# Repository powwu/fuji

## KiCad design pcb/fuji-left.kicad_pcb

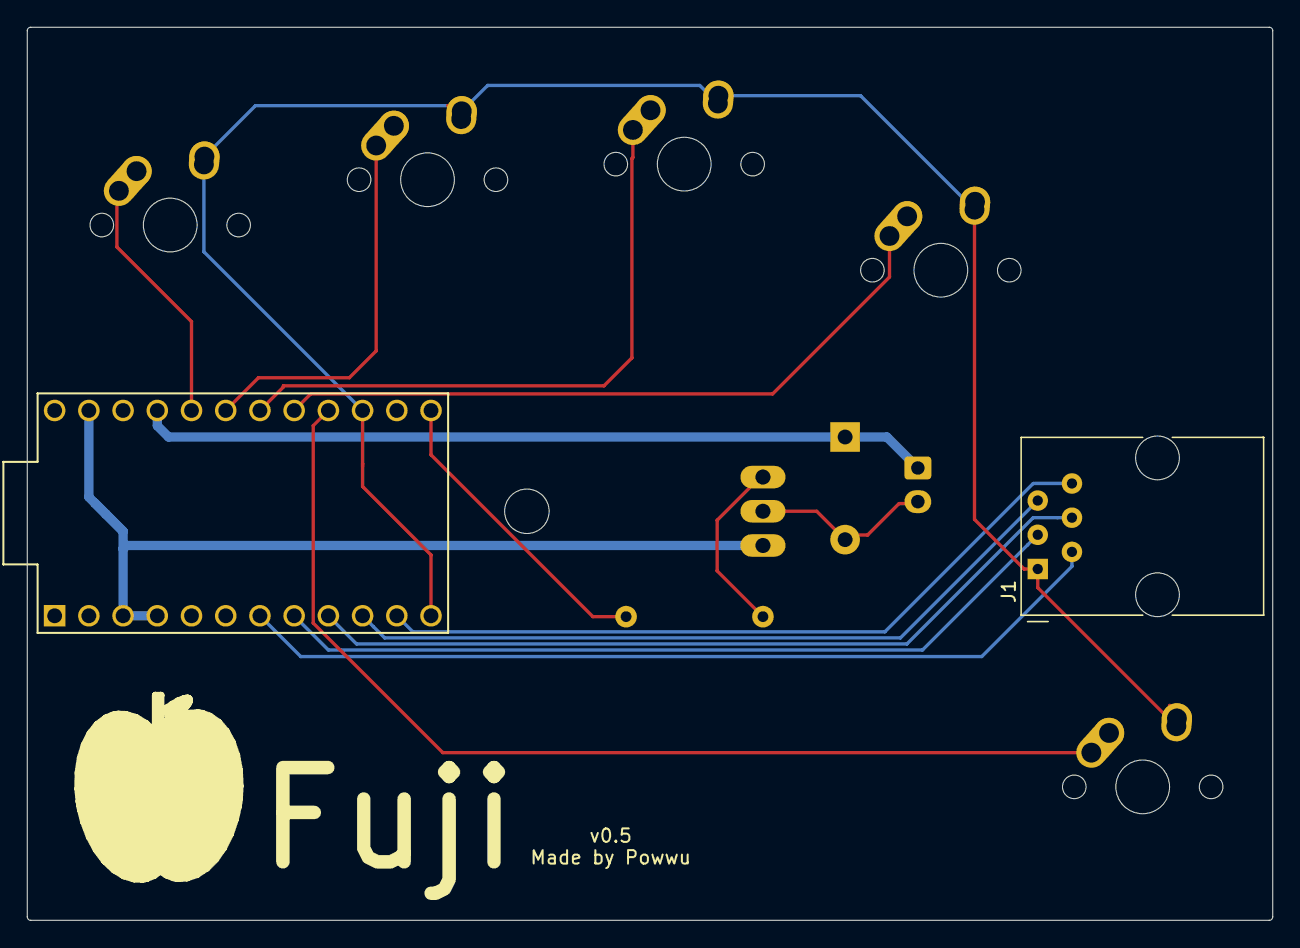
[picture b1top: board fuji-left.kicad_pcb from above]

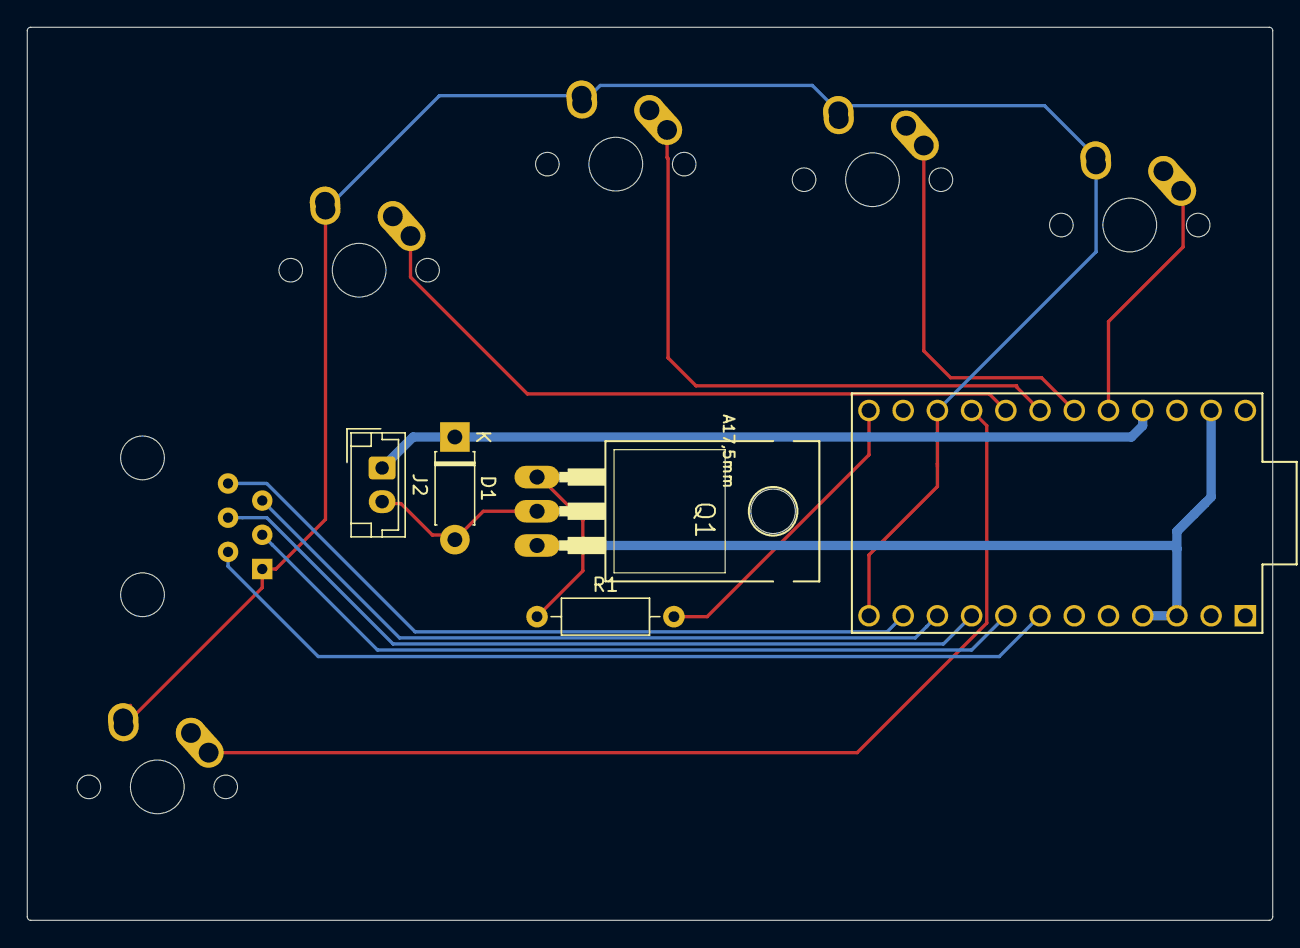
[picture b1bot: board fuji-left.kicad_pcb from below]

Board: 2 copper layers, 92.5 x 66.3 mm, 11 parts (4 on the bottom side), 16 nets.

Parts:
D1: 1N4004; D_DO-41_SOD81_P7.62mm_Horizontal
J1: 6P6C; RJ12_Amphenol_54601
J2: SOLENOID JST; JST_EH_B2B-EH-A_1x02_P2.50mm_Vertical
MX1, MX2, MX3, MX4, MX5: MX-NoLED; MX-1U-NoLED
Q1: TIP120; TO220AH
R1: 1.0K; R_Axial_DIN0207_L6.3mm_D2.5mm_P10.16mm_Horizontal
U1: kbd_ProMicro; ProMicro

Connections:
COL0: MX5.1, U1.16
COL1: MX4.1, U1.17
COL2: MX3.1, U1.18
COL3: MX2.1, U1.19
COL4: MX1.1, U1.20
COL5: J1.6, U1.11
COL6: J1.5, U1.10
COL7: J1.4, U1.9
COL8: J1.3, U1.8
COL9: J1.2, U1.7
GND: Q1.E, U1.3, U1.4, U1.23
unnamed: D1.2, J2.2, Q1.C
unnamed: Q1.B, R1.1
ROW0: J1.1, MX1.2, MX2.2, MX3.2, MX4.2, MX5.2, U1.12, U1.15
SOL: R1.2, U1.13
VCC: D1.1, J2.1, U1.21

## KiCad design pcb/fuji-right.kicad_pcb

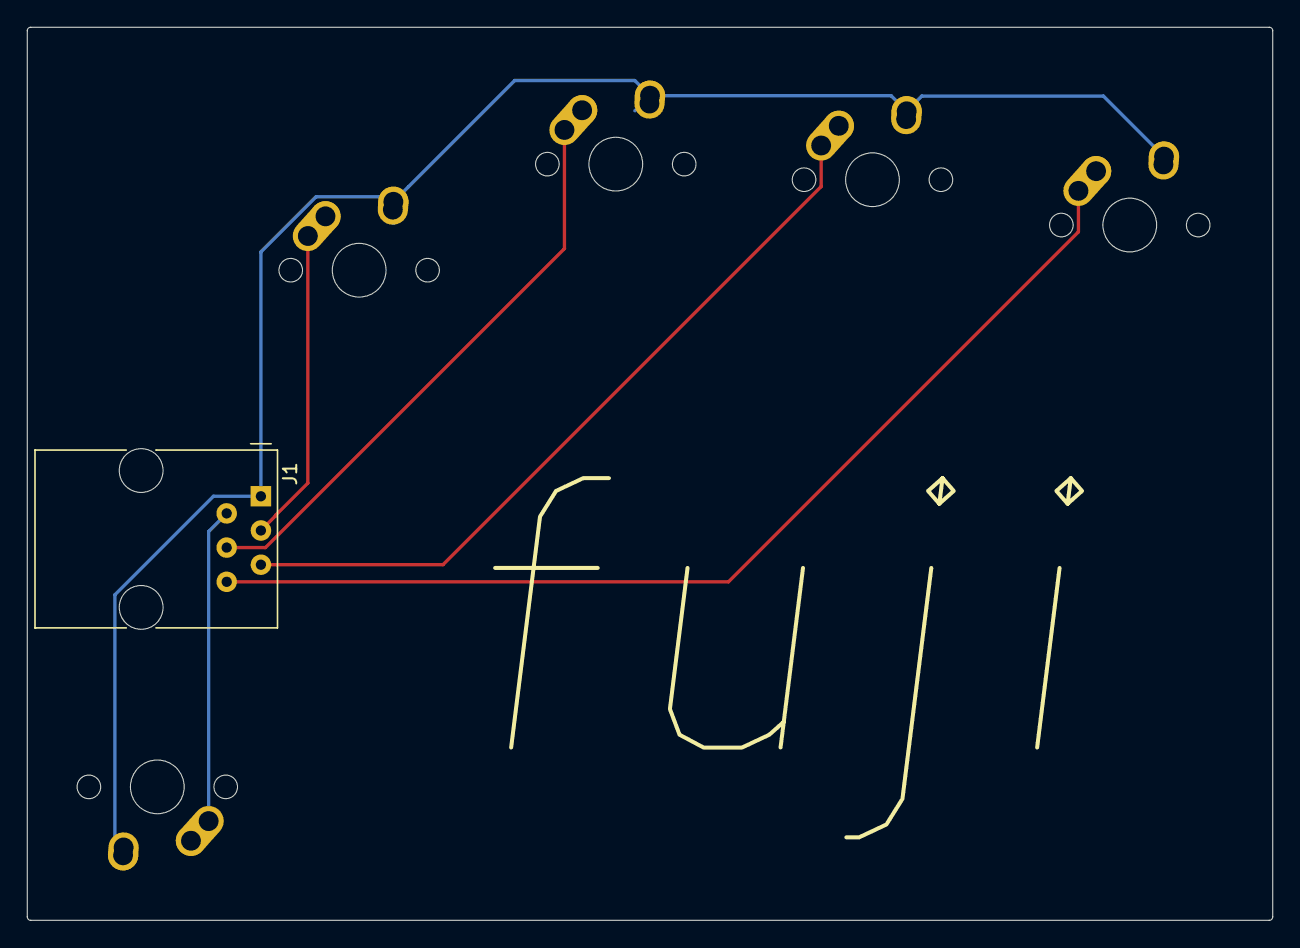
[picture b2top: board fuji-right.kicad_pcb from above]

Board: 2 copper layers, 92.5 x 66.3 mm, 6 parts (0 on the bottom side), 6 nets.

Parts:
J1: 6P6C; RJ12_Amphenol_54601
MX1, MX2, MX3, MX4, MX5: MX-NoLED; MX-1U-NoLED

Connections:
COL5: J1.2, MX5.1
COL6: J1.3, MX4.1
COL7: J1.4, MX3.1
COL8: J1.5, MX2.1
COL9: J1.6, MX1.1
ROW0: J1.1, MX1.2, MX2.2, MX3.2, MX4.2, MX5.2

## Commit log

2022-11-18 v2 woooo
